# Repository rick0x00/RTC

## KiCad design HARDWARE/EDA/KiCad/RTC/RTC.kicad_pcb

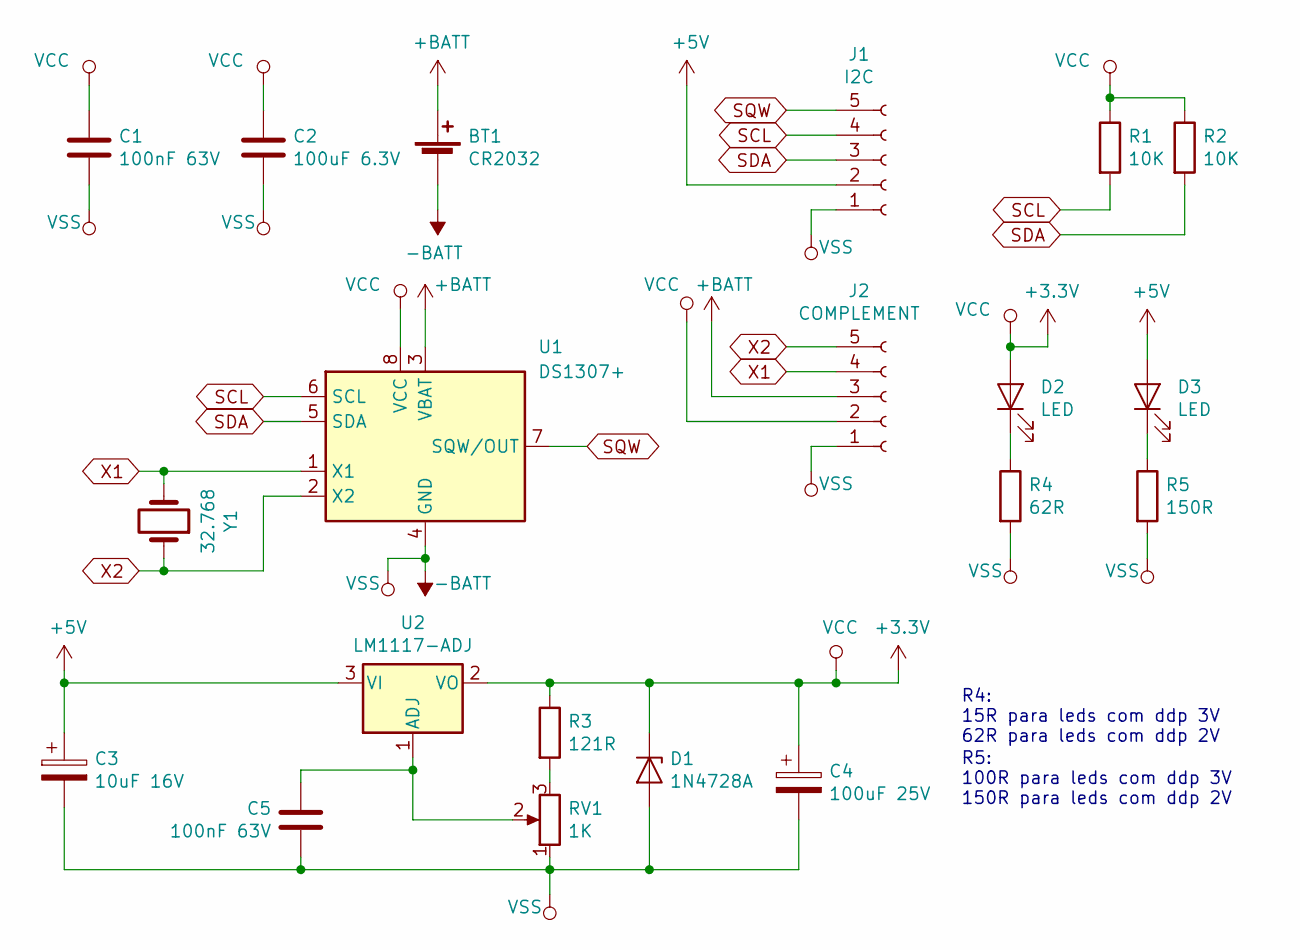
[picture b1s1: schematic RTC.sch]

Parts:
BT1: CR2032; BatteryHolder_Keystone_1060_1x2032
C1, C5: 100nF 63V; C_Rect_L7.2mm_W2.5mm_P5.00mm_FKS2_FKP2_MKS2_MKP2
C2: 100uF 6.3V; CP_Radial_D4.0mm_P2.00mm
C3: 10uF 16V; CP_Radial_D5.0mm_P2.00mm
C4: 100uF 25V; CP_Radial_D5.0mm_P2.50mm
D1: 1N4728A; D_DO-41_SOD81_P10.16mm_Horizontal
D2, D3: LED; LED_D5.0mm
J1: I2C; PinHeader_1x05_P2.54mm_Horizontal
J2: COMPLEMENT; PinHeader_1x05_P2.54mm_Horizontal
R1, R2: 10K; R_Axial_DIN0207_L6.3mm_D2.5mm_P7.62mm_Horizontal
R3: 121R; R_Axial_DIN0207_L6.3mm_D2.5mm_P7.62mm_Horizontal
R4: 62R; R_Axial_DIN0207_L6.3mm_D2.5mm_P7.62mm_Horizontal
R5: 150R; R_Axial_DIN0207_L6.3mm_D2.5mm_P7.62mm_Horizontal
RV1: 1K; Potentiometer_Bourns_3296Y_Vertical
U1: DS1307+; DIP-8_W7.62mm
U2: LM1117-ADJ; TO-220-3_Vertical
Y1: 32.768; Crystal_C26-LF_D2.1mm_L6.5mm_Horizontal_1EP_style2

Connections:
+3V3: C1.1, C2.1, C4.1, D1.1 (K), D2.2 (A), J2.2, R1.1, R2.1, R3.1, U1.8 (VCC), U2.2 (VO)
+5V: C3.1, D3.2 (A), J1.2, U2.3 (VI)
+BATT: BT1.1 (+), J2.3, U1.3 (VBAT)
-BATT: BT1.2 (-), C1.2, C2.2, C3.2, C4.2, C5.2, D1.2 (A), J1.1, J2.1, R4.2, R5.2, RV1.1, U1.4 (GND)
unnamed: C5.1, RV1.2, U2.1 (ADJ)
unnamed: D2.1 (K), R4.1
unnamed: D3.1 (K), R5.1
unnamed: R3.2, RV1.3
SCL: J1.4, R1.2, U1.6 (SCL)
SDA: J1.3, R2.2, U1.5 (SDA)
SQW: J1.5, U1.7 (SQW/OUT)
X1: J2.4, U1.1 (X1), Y1.2
X2: J2.5, U1.2 (X2), Y1.1

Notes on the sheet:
R5: 100R para leds com ddp 3V 150R para leds com ddp 2V
R4: 15R para leds com ddp 3V 62R para leds com ddp 2V

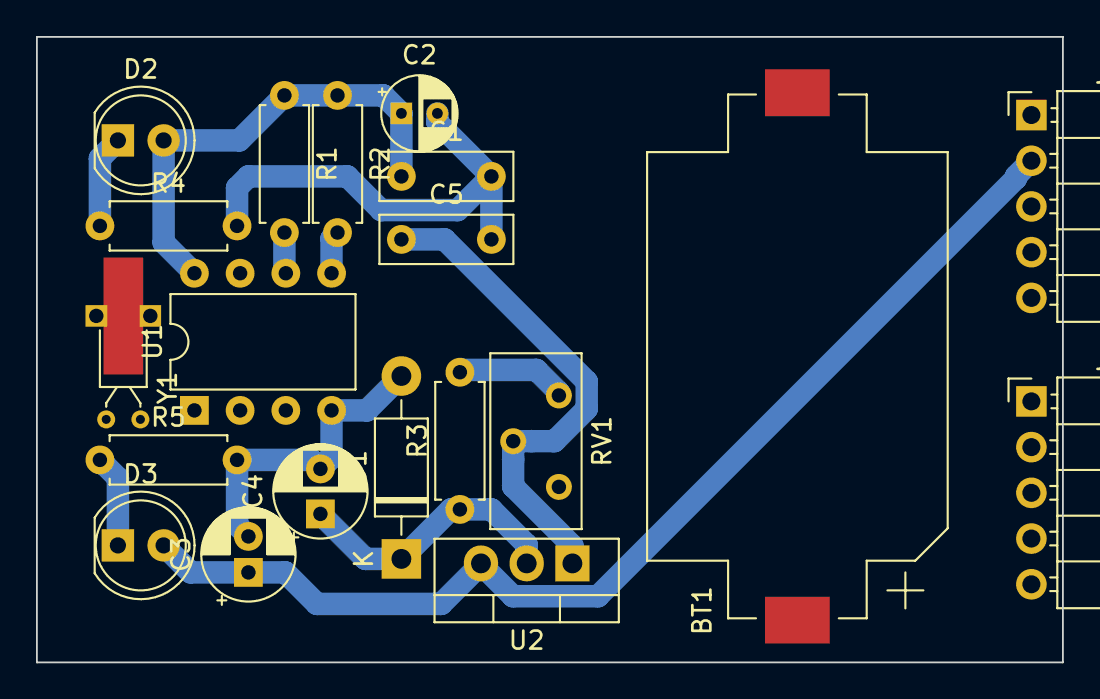
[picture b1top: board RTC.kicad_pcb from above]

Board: 2 copper layers, 57.0 x 34.8 mm, 20 parts (0 on the bottom side), 13 nets.

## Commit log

2021-12-13 start project
2021-12-13 pause woerk
2021-12-13 finished footprints associates with
2021-12-13 fix trimpot footprint
2021-12-14 pause project
2022-01-03 review pcb design
